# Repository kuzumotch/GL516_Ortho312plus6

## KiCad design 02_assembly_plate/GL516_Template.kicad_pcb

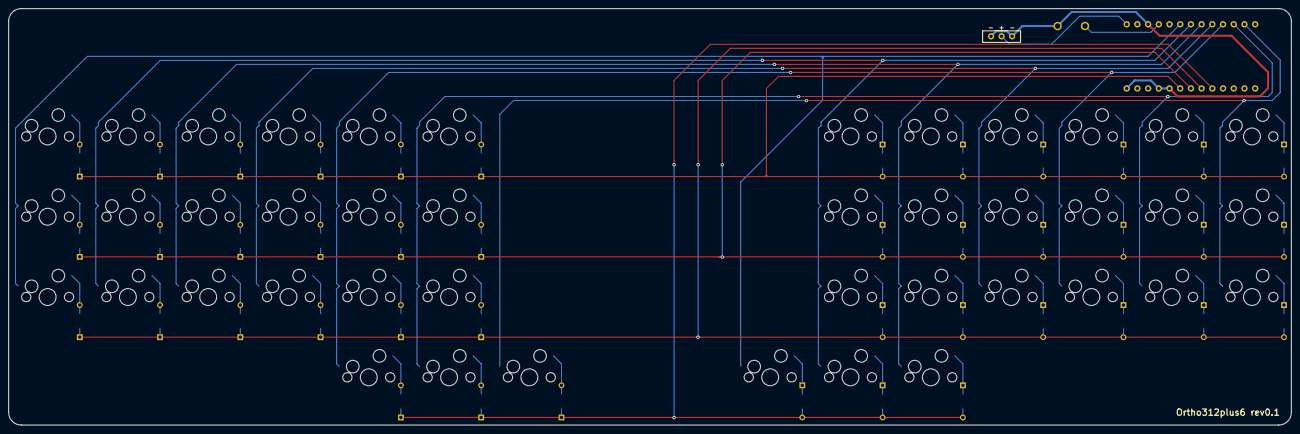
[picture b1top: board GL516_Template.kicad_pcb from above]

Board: 2 copper layers, 304.4 x 98.8 mm, 87 parts (1 on the bottom side), 56 nets.

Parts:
D1, D2, D3, D4, D5, D6, D7, D8, D9, D10, D11, D12, D13, D14, D15, D16, D17, D18, D19, D20, D21, D22, D23, D24, D25, D26, D27, D28, D29, D30, D31, D32, D33, D34, D35, D36, D37, D38, D39, D40, D41, D42: D; Diode_TH_SMD
J1: Conn_01x02; Battery_XH2.5_GL_PCB
SW1, SW2, SW3, SW4, SW5, SW6, SW7, SW8, SW9, SW10, SW11, SW12, SW13, SW14, SW15, SW16, SW17, SW18, SW19, SW20, SW21, SW22, SW23, SW24, SW25, SW26, SW27, SW28, SW29, SW30, SW31, SW32, SW33, SW34, SW35, SW36, SW37, SW38, SW39, SW40, SW41, SW42: SW_PUSH; CherryMX_Hotswap_1.0u
SW43: SW_PUSH; ResetSW
U1: BLEMicroPro; Micon_BMP_GL

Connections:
Bat+: J1.1, U1.25
Col0: SW1.1, SW2.1, SW3.1, SW22.1, U1.20
Col1: SW4.1, SW5.1, SW6.1, SW23.1, SW24.1, SW25.1, SW26.1, U1.19
Col2: SW7.1, SW8.1, SW9.1, SW27.1, SW28.1, SW29.1, SW30.1, U1.18
Col3: SW10.1, SW11.1, SW12.1, SW31.1, SW32.1, SW33.1, U1.17
Col4: SW13.1, SW14.1, SW15.1, SW16.1, SW34.1, SW35.1, SW36.1, U1.16
Col5: SW17.1, SW18.1, SW19.1, SW20.1, SW37.1, SW38.1, SW39.1, U1.15
Col6: SW21.1, SW40.1, SW41.1, SW42.1, U1.14
GND: J1.2, SW43.2, U1.3, U1.4, U1.23, U1.26
unnamed: D1.2, SW1.2
unnamed: D2.2, SW2.2
unnamed: D3.2, SW3.2
unnamed: D4.2, SW4.2
unnamed: D5.2, SW5.2
unnamed: D6.2, SW6.2
unnamed: D7.2, SW7.2
unnamed: D8.2, SW8.2
unnamed: D9.2, SW9.2
unnamed: D10.2, SW10.2
unnamed: D11.2, SW11.2
unnamed: D12.2, SW12.2
unnamed: D13.2, SW13.2
unnamed: D14.2, SW14.2
unnamed: D15.2, SW15.2
unnamed: D16.2, SW16.2
unnamed: D17.2, SW17.2
unnamed: D18.2, SW18.2
unnamed: D19.2, SW19.2
unnamed: D20.2, SW20.2
unnamed: D21.2, SW21.2
unnamed: D22.1, SW22.2
unnamed: D23.1, SW23.2
unnamed: D24.1, SW24.2
unnamed: D25.1, SW25.2
unnamed: D26.1, SW26.2
unnamed: D27.1, SW27.2
unnamed: D28.1, SW28.2
unnamed: D29.1, SW29.2
unnamed: D30.1, SW30.2
unnamed: D31.1, SW31.2
unnamed: D32.1, SW32.2
unnamed: D33.1, SW33.2
unnamed: D34.1, SW34.2
unnamed: D35.1, SW35.2
unnamed: D36.1, SW36.2
unnamed: D37.1, SW37.2
unnamed: D38.1, SW38.2
unnamed: D39.1, SW39.2
unnamed: D40.1, SW40.2
unnamed: D41.1, SW41.2
unnamed: D42.1, SW42.2
Reset: SW43.1, U1.22
Row0: D1.1, D4.1, D7.1, D10.1, D13.1, D17.1, D23.2, D27.2, D31.2, D34.2, D37.2, D40.2, U1.5
Row1: D2.1, D5.1, D8.1, D11.1, D14.1, D18.1, D24.2, D28.2, D32.2, D35.2, D38.2, D41.2, U1.6
Row2: D3.1, D6.1, D9.1, D12.1, D15.1, D19.1, D25.2, D29.2, D33.2, D36.2, D39.2, D42.2, U1.7
Row3: D16.1, D20.1, D21.1, D22.2, D26.2, D30.2, U1.8

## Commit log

2021-08-04 Create top plate directory
2021-08-04 add dxf file
2021-08-04 Finish Creating Top Plate Project
2021-08-04 Make Relation Between Footprint and Symbols
2021-08-04 place all footprints and change edge.cuts
2021-08-04 change position of silks for D40 - D42
2021-08-04 change position of silks for D40 - D42 again
2021-08-04 Wire GND, RST, BAT+
2021-08-04 Wire Diode's PAT and Pin Hole
2021-08-04 Wire SW Socket's 2nd Pats and Diodes
2021-08-04 Wire Col
2021-08-04 Finish All Wiring
2021-08-04 Something on Kairo-zu updated
2021-08-04 Top Plate Nuri-tsubushi and logo
2021-08-04 Remove Logo Library to extern and edit logo a bit
2021-08-05 fix wiring
2021-08-05 fix logo on Top Plate
2021-08-05 add version text on both Top and Assembly Plates
2021-08-06 add battery + - silk / mod version
